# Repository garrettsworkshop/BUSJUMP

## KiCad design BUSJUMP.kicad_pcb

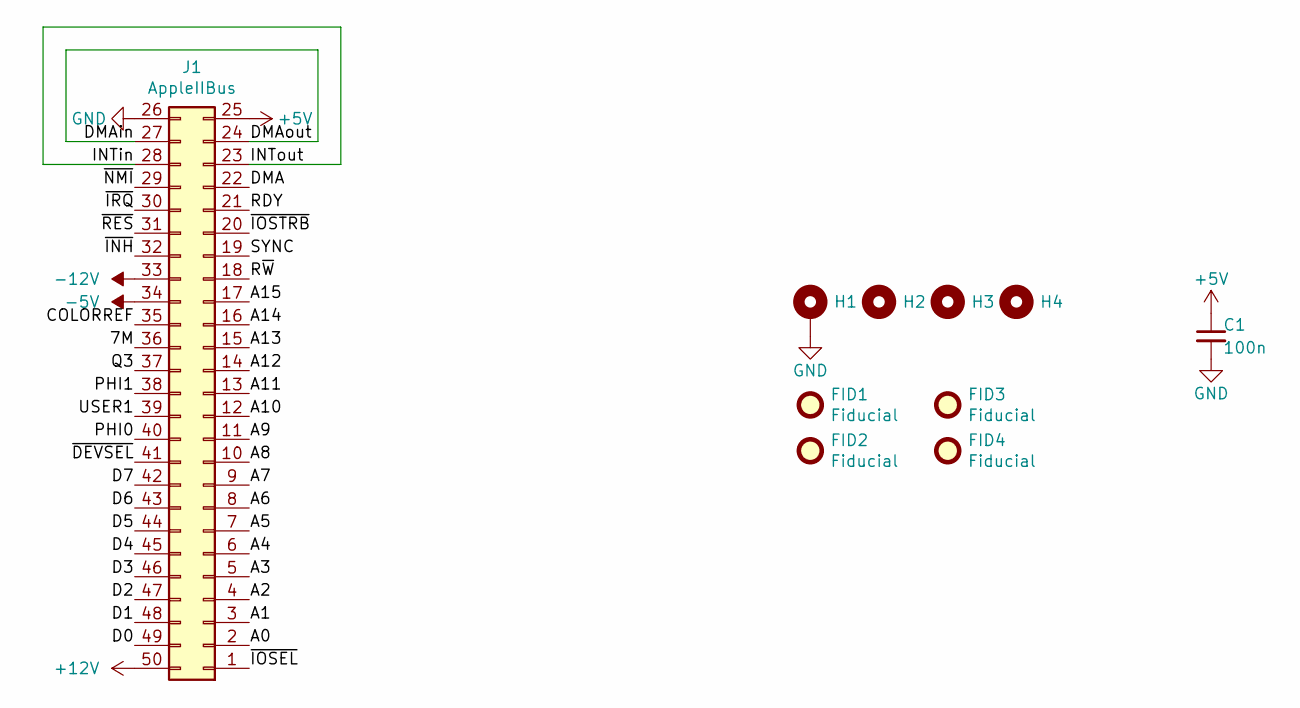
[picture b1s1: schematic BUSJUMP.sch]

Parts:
C1: 100n; C_0805
FID1, FID2, FID3, FID4: Fiducial
H1: PasteHole_1.05mm_PTH
H2, H3, H4: PasteHole_1.05mm_NPTH
J1: AppleIIBus; AppleIIBus_Edge

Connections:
+5V: C1.1, J1.25
+12V: J1.50
-5V: J1.34
-12V: J1.33
/7M: J1.36
/A0: J1.2
/A1: J1.3
/A2: J1.4
/A3: J1.5
/A4: J1.6
/A5: J1.7
/A6: J1.8
/A7: J1.9
/A8: J1.10
/A9: J1.11
/A10: J1.12
/A11: J1.13
/A12: J1.14
/A13: J1.15
/A14: J1.16
/A15: J1.17
/COLORREF: J1.35
/D0: J1.49
/D1: J1.48
/D2: J1.47
/D3: J1.46
/D4: J1.45
/D5: J1.44
/D6: J1.43
/D7: J1.42
/DMA: J1.22
/DMAin: J1.24, J1.27
/INTin: J1.23, J1.28
/PHI0: J1.40
/PHI1: J1.38
/Q3: J1.37
/RDY: J1.21
/R~W~: J1.18
/SYNC: J1.19
/USER1: J1.39
/~DEVSEL~: J1.41
/~INH~: J1.32
/~IOSEL~: J1.1
/~IOSTRB~: J1.20
/~IRQ~: J1.30
/~NMI~: J1.29
/~RES~: J1.31
GND: C1.2, H1.1, J1.26

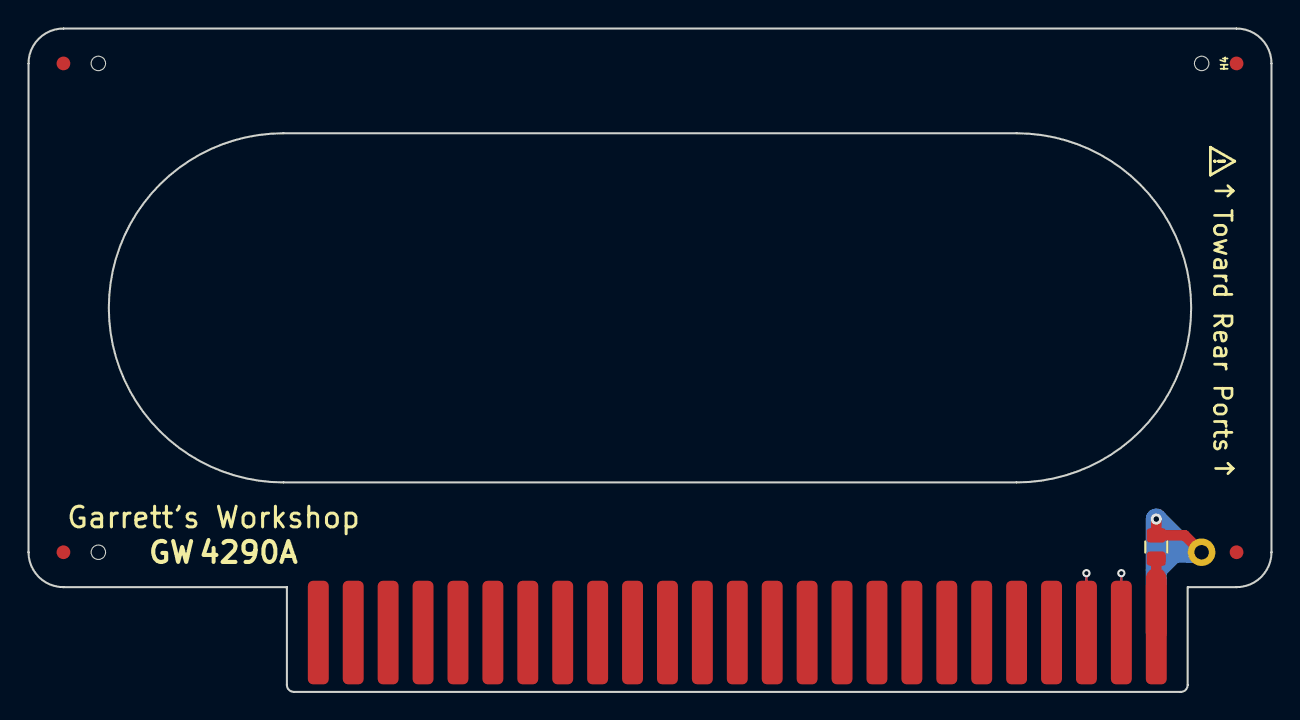
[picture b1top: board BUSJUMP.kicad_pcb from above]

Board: 2 copper layers, 90.4 x 48.3 mm, 10 parts (0 on the bottom side), 4 nets.

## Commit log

2019-07-21 BUSJUMP
2019-07-21 Added schematic PDF
